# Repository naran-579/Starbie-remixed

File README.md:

# Starbie remixed
Modified version of hack club's Starbie starter project

# What I changed:

- Changed shape from blocky to smooth and sharp
- Had to rearrange the components to better wire it
- Much more "unique" wiring layout (this is my first time doing this ok)
- A BATTERY!!!!!!!!!
- AN LED!!!!
- Temperature now impacts the starbie more

## THE LED

Rapid blinks = BATTERY VERY LOW.  
Off = Sleep mode.  
Two quick blinks every 2 seconds = Battery low.  
one blink every 4 secs = starbie napping :D.  
SOlid on = Just after play/pet.  
Three quick blinks every 3 secs = Starbie is hot.  
A stutter and a pause every 3 secs = Starbie is cold.  
A blink every 3 seconds = Starbie is happy.  
A blink every 6 secs = Starbie is okay (pretty much middlish happiness).  
A slow glow every 8 secs = Starbie is sad.  

## THE BATTERY

3xAAs. 

# BOM

| Item                     | Qty | Supplier   | Cost/item | Total Cost | link                                                                                                                                                                                                                                                                                                                                                                                                                                                                                                                                                                                                                                                                                                                                              |
|--------------------------|-----|------------|-----------|------------|---------------------------------------------------------------------------------------------------------------------------------------------------------------------------------------------------------------------------------------------------------------------------------------------------------------------------------------------------------------------------------------------------------------------------------------------------------------------------------------------------------------------------------------------------------------------------------------------------------------------------------------------------------------------------------------------------------------------------------------------------|
| MPU6050                  | 1   | Nextronics | $1.09     | $1.09      | https://www.aliexpress.us/item/3256812536361672.html?spm=a2g0o.productlist.main.3.687f3357baFQaZ&algo_pvid=b8863c80-f236-4e2a-9be2-ca5d876ab6d7&algo_exp_id=b8863c80-f236-4e2a-9be2-ca5d876ab6d7-2&pdp_ext_f=%7B%22order%22%3A%22273%22%2C%22eval%22%3A%221%22%2C%22fromPage%22%3A%22search%22%7D&pdp_npi=6%40dis%21USD%213.86%211.09%21%21%2125.73%217.28%21%402101ca8b17917628147636139e11fe%2112000059167286842%21sea%21US%210%21ABX%211%210%21n_tag%3A-29910%3Bd%3A5adf47b2%3Bm03_new_user%3A-29895%3BpisId%3A5000000218165385&curPageLogUid=CeT4F0H16d6d&utparam-url=scene%3Asearch%7Cquery_from%3A%7Cx_object_id%3A1005012722676424%7C_p_origin_prod%3A                                                                                     |
| LED                      | 1   | Sparkfun   | $0.50     | $0.50      | https://www.sparkfun.com/led-basic-yellow-5mm.html                                                                                                                                                                                                                                                                                                                                                                                                                                                                                                                                                                                                                                                                                                |
| DHT11                    | 1   | SUZpng     | $1.09     | $1.09      | https://www.aliexpress.us/item/3256812076791904.html?spm=a2g0o.productlist.main.4.6ce61b79Z6F1N5&aem_p4p_detail=2026101117033112883497543879100002439632&algo_pvid=b9188a67-e63a-42ce-9186-041aba5586ad&algo_exp_id=b9188a67-e63a-42ce-9186-041aba5586ad-3&pdp_ext_f=%7B%22order%22%3A%2264%22%2C%22eval%22%3A%221%22%2C%22fromPage%22%3A%22search%22%7D&pdp_npi=6%40dis%21USD%211.12%211.12%21%21%217.44%217.44%21%402101e80f17917634115724335e0f86%2112000057911460838%21sea%21US%210%21ABX%211%210%21n_tag%3A-29910%3Bd%3A5adf47b2%3Bm03_new_user%3A-29895&curPageLogUid=bDmfpBt8K9fZ&utparam-url=scene%3Asearch%7Cquery_from%3A%7Cx_object_id%3A1005012263106656%7C_p_origin_prod%3A&search_p4p_id=2026101117033112883497543879100002439632_1 |
| Schottky diode           | 1   | Digikey    | $0.29     | $0.29      | https://www.digikey.com/en/products/detail/1N5817-TP/1N5817-TPCT-ND/950586                                                                                                                                                                                                                                                                                                                                                                                                                                                                                                                                                                                                                                                                        |
| SPDT slide switch        | 1   | Sparkfun   | $1.75     | $1.75      | https://www.sparkfun.com/mini-power-switch-spdt.html                                                                                                                                                                                                                                                                                                                                                                                                                                                                                                                                                                                                                                                                                              |
| resistors                | 1   | ONJYHK     | $9.99     | $9.99      | https://www.amazon.com/ONJYHK-100Values-Resistor-Resistors-Assortment/dp/B0GJYDKNPC/ref=sr_1_1_sspa?crid=14XFMN4ZP5P3K&dib=eyJ2IjoiMSJ9.QqtzmCG7CKt6OW1fHgTb26uI1Fk5beBArSayNzxiB8QctNAGQjh0FV4BhmaNPqIxh81Ijafj0OsSJwFLaxzxF0p9l_Xm_7Y1iwtiJvwHQma0hmE_EBQMZp989mBgppQ7jrAx4siNhzSjsGfM-3A5KBYFvkOsaxwDGKunj-pCgjYjUxRNjIBuDyb3_2YtBk_toT2rD0okAfK05DhA4sgDkDFNgjavmUCwJV_ZryuUSQ4.E4jJD8OwA8a17JnTFmhe7njpVAWsAdqWxeoOJJ2OwfE&dib_tag=se&keywords=resistor+assortment&qid=1791763710&sprefix=resistor+assortment%2Caps%2C197&sr=8-1-spons&sp_csd=d2lkZ2V0TmFtZT1zcF9hdGY&psc=1                                                                                                                                                                  |
| Keyswitches              | 2   | Digikey    | $1.75     | $3.50      | https://www.digikey.com/en/products/detail/cherry-americas-llc/MX2A-E1NA/21738437                                                                                                                                                                                                                                                                                                                                                                                                                                                                                                                                                                                                                                                                 |
| PCB                      | 1   | JLPCB      | $14.30    | $14.30     | https://cart.jlcpcb.com/quote?quoteTab=standardPcb&_t=1791764704116&spm=Jlcpcb.Instantquote.1005&up_spm=Jlcpcb.Loginpage.1003                                                                                                                                                                                                                                                                                                                                                                                                                                                                                                                                                                                                                     |
| ESP32C3                  | 1   | SeedStudio | $5.90     | $5.90      | https://www.seeedstudio.com/Seeed-Studio-XIAO-ESP32C3-Pre-Soldered-p-6331.html                                                                                                                                                                                                                                                                                                                                                                                                                                                                                                                                                                                                                                                                    |
| OLED                     | 1   | HiLetGo    | $6.99     | $6.99      | https://www.amazon.com/HiLetgo-Serial-128X64-Display-Color/dp/B06XRBTBTB/ref=sr_1_20?crid=REZOFNY2DSMW&dib=eyJ2IjoiMSJ9.6uJuI5cggaMKzcvI3mu-dhpquj-AamHKVU-jNYahS3r7KPQ4rP9MWcpO3VgxtiVrg_OkzAn_QbQ7Hdf6zH10hly_XEUirYsm0spkmSrpY_q-tg1zEhBPSos8FHFjgka5SuaJx1bsu5j_3YamNvVc-XHqDicf1QvC1Pj9Fdzrv5G1q018QTntw4HlZc5jG7M6U6iGu-HOrbsx8lAwk-fmsQ4zyk0cUqZL81wx6wdBnW8.DTtm6svRmhp9loB64gXCSxWrcMJlM0Zb-affLb91XGw&dib_tag=se&keywords=0.96+inch+oled&qid=1792945681&sprefix=0.96+inch+oled%2Caps%2C164&sr=8-20                                                                                                                                                                                                                                      |
| aa battery holders       | 1   | Amazon     | $4.99     | $4.99      | https://www.amazon.com/AOICRIE-Single-Battery-8PCS-1AA/dp/B09ZYFRTL5/ref=sr_1_4?crid=7M1XEMT4U6Q9&dib=eyJ2IjoiMSJ9.I-D8x9sU5SAvqMCck_PqZsrwt9N5MLl5C-60yxM-W5jgeuNja8WWyPwaUA8lQ4sS8x5OsgxDRNbNA5ZfCCOHPpZYGav31QMtpYLuOKpMVBrBsXvX1ErpF_mIWvAChYiCMYVyUFvJN9cBc5h-C60VBcadBgoMVjbT4hyBBDfHXvjihp7q5u-8Z8lD5fj85Fk34L0ULwxCEYZYspfh3V6Rnum6gwK_btk-NgNzWkiIvxo.E3bCfnxlETyCG8SmMttUqZ9AIZCEGeWdOe7nqwopN0E&dib_tag=se&keywords=1+aa+battery+holder&qid=1792946507&sprefix=1+aa+battery+holder%2Caps%2C240&sr=8-4                                                                                                                                                                                                                                  |
| AA batteries             | 1   | Enegizer   | $4.97     | $4.97      | https://www.amazon.com/Energizer-MAX-Alkaline-Batteries-Pack/dp/B00451SSBI/ref=sr_1_28?crid=2OR76XFIZVXAL&dib=eyJ2IjoiMSJ9.9BhQMbW-D1k7f1etQtjFXvJBtu8YwnW1_ZBYByE3kMj31KTCa_gNWC57fUKthuzrrb6dHqPOUH6D9Bo9ty7DgR3IVBeHbVw27R8B68xsB7r7tpzYMOdziYQx93JG-hGAxDcfiW-nPHa2q4hfwCQ1kw0n77tPF4es3XMOvHusc2_zNIYZCKcn6GmMdz7Lpiqm8lZYbG2FUNhbySl0fIIaK4QYU7Sm1Ds_nH9wBuPXHUuijjHcord2Qz9hHstPv4MMLcPwYslaopiGdMBc_oX82WCLPV0JlE8-citnBHEzjjw.rIMc54liLYLpdYv6_38sJwKtPD2IWxu0_AmFEFX2Ct0&dib_tag=se&keywords=aa+batteries&qid=1792946573&sprefix=aa+batterie%2Caps%2C223&sr=8-28                                                                                                                                                                        |
| Estimated total shipping | 1   |            |           | $0.26      |                                                                                                                                                                                                                                                                                                                                                                                                                                                                                                                                                                                                                                                                                                                                                   |

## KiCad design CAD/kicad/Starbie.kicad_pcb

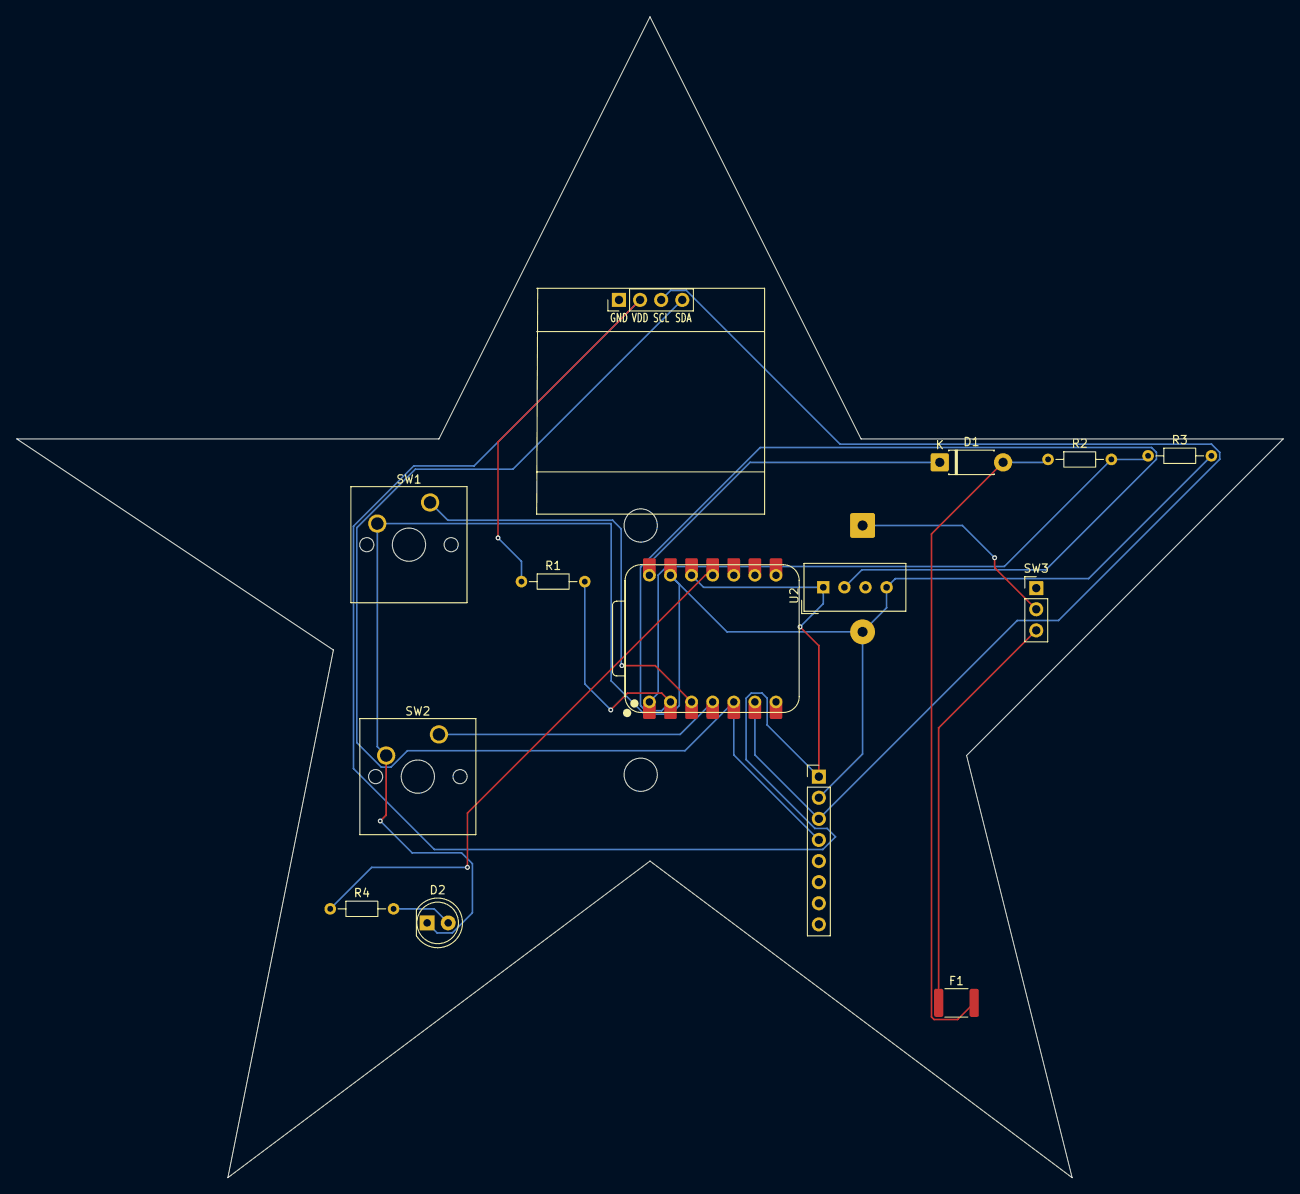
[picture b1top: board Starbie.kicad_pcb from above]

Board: 2 copper layers, 152.4 x 139.7 mm, 15 parts (1 on the bottom side), 14 nets.

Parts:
D1: D_Schottky; D_DO-41_SOD81_P7.62mm_Horizontal
D2: LED; LED_D5.0mm
F1: Polyfuse; Fuse_1812_4532Metric
J1: Conn_01x04_Pin; Display_128x64_096_I2C
J2: Conn_01x08_Pin; PinHeader_1x08_P2.54mm_Vertical
J3: Conn_01x02; BatteryHolder_TruPower_BH-331P_3xAA
R1: 10k; R_Axial_DIN0204_L3.6mm_D1.6mm_P7.62mm_Horizontal
R2: 100k; R_Axial_DIN0204_L3.6mm_D1.6mm_P7.62mm_Horizontal
R3: 47k; R_Axial_DIN0204_L3.6mm_D1.6mm_P7.62mm_Horizontal
R4: 330; R_Axial_DIN0204_L3.6mm_D1.6mm_P7.62mm_Horizontal
SW1, SW2: SW_Push; SW_Cherry_MX_1.00u_PCB
SW3: SW_SPDT; PinHeader_1x03_P2.54mm_Vertical
U1: XIAO-ESP32-C3-SMD; XIAO-ESP32-C6-DIP
U2: DHT11; Aosong_DHT11_5.5x12.0_P2.54mm

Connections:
+3.3V: J1.2, J2.1, R1.1, U1.12 (3V3_OUT), U2.1 (VDD)
+5V: D1.1 (K), U1.14 (VBUS)
/BAT_SENSE: R2.2, R3.1, U1.1 (D0)
/Battery+: J3.1, SW3.2 (B)
/Button 1 Net: SW1.1, U1.3 (D2)
/Button 2 Net: SW2.1, U1.4 (D3)
/DHT11 DATA: R1.2, U1.2 (D1), U2.2 (DATA)
/LED: R4.1, U1.11 (D10)
/SCL: J1.3, J2.3, U1.6 (D5)
/SDA: J1.4, J2.4, U1.5 (D4)
/VBAT: D1.2 (A), F1.2, R2.1
GND: D2.1 (K), J1.1, J2.2, J3.2, R3.2, SW1.2, SW2.2, U1.13 (GND), U2.4 (GND)
unnamed: D2.2 (A), R4.2
unnamed: F1.1, SW3.3 (C)
